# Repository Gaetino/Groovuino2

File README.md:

# Groovuino2

New version of groovuino

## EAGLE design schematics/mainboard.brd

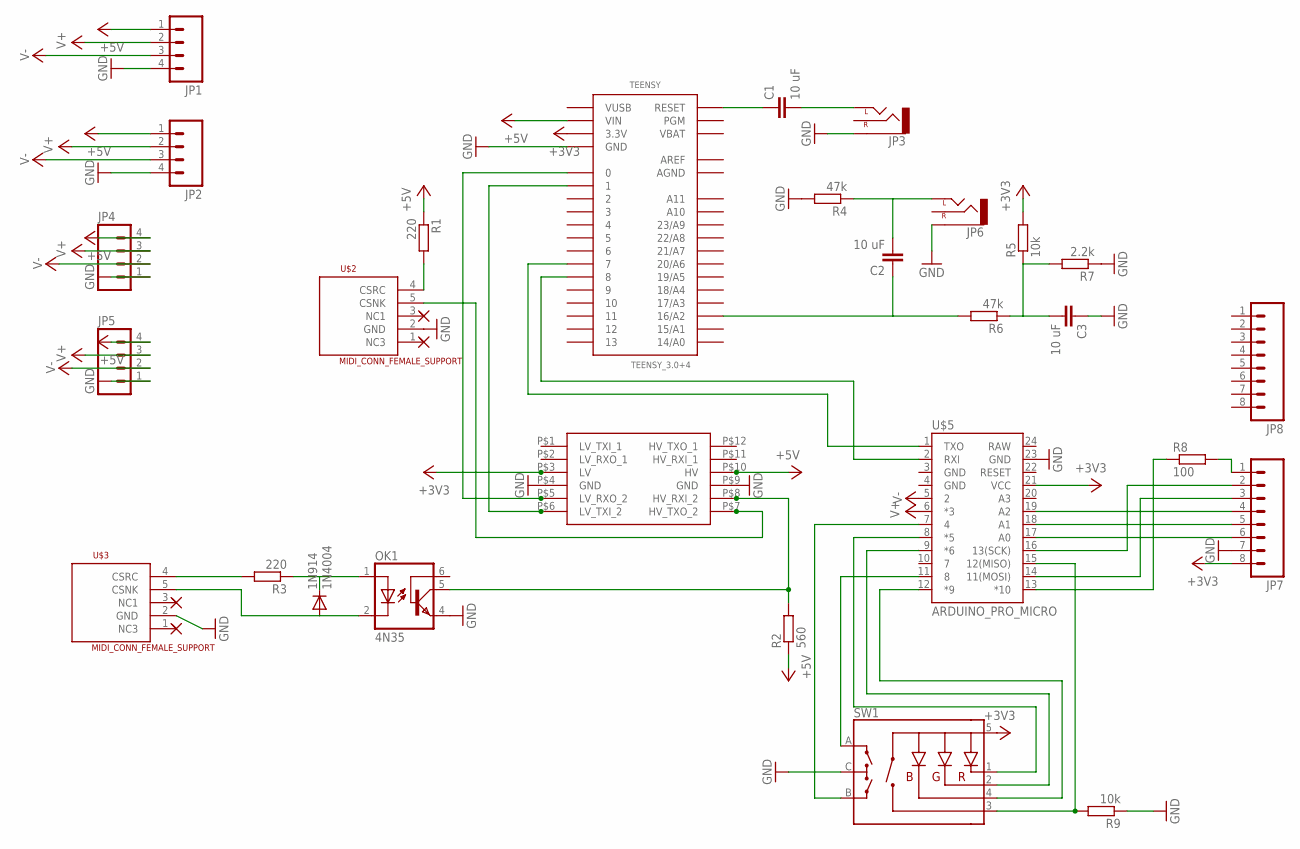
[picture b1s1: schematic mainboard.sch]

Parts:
1N914: 1N4004; DO41-10
C1, C2, C3: 10 uF; CAP-PTH-SMALL
JP1, JP2, JP4, JP5: M04PTH; 1X04
JP3, JP6: AUDIO-JACKPTH; AUDIO-JACK
JP7, JP8: M08; 1X08_ROUND
OK1: 4N35; DIL06
R1, R3: 220; 0204/5
R2: 560; 0204/5
R4, R6: 47k; 0204/5
R5, R9: 10k; 0204/5
R7: 2.2k; 0204/5
R8: 100; 0204/5
SW1: ENCODER_RGB_CA; ENCODER_LED_3
TEENSY: TEENSY_3.0+4
U$2, U$3: MIDI_CONN_FEMALE_SUPPORT; DIN_5_FEMALE_SUPPORT
U$4: LOGIC_LEVEL_CONVERTER
U$5: ARDUINO_PRO_MICRO

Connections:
+3V3: JP7.8, R5.2, SW1.5 (+), TEENSY.3.3V, TEENSY.3.3V1 (3.3V), U$4.P$3 (LV), U$5.21 (VCC)
+5V: JP1.1, JP2.1, JP4.4, JP5.4, R1.1, R2.1, TEENSY.VIN, U$4.P$10 (HV)
AGND: TEENSY.AGND
AREF: TEENSY.AREF
GND: C3.1, JP1.4, JP2.4, JP3.SLEEVE, JP4.1, JP5.1, JP6.SLEEVE, JP7.7, OK1.4 (EMI), R4.2, R7.1, R9.1, SW1.C, TEENSY.GND, TEENSY.GND1 (GND), U$2.2 (GND), U$3.2 (GND), U$4.P$4 (GND), U$4.P$9 (GND), U$5.23 (GND)
unnamed: C1.1, TEENSY.RESET
unnamed: OK1.5 (COL), R2.2, U$4.P$8 (HV_RXI_2)
unnamed: JP7.1, R8.2
unnamed: C1.2, JP3.TIP (LEFT)
unnamed: C2.2, JP6.TIP (LEFT), R4.1
unnamed: C2.1, R6.2, TEENSY.16/A2
unnamed: C3.2, R5.1, R6.1, R7.2
unnamed: R3.2, U$3.4 (CSRC)
unnamed: SW1.2 (-G), U$5.9 (*6)
unnamed: TEENSY.7, U$5.1 (TXO)
unnamed: TEENSY.8, U$5.2 (RXI)
unnamed: SW1.1 (-R), U$5.8 (*5)
unnamed: SW1.A, U$5.11 (8)
unnamed: U$2.5 (CSNK), U$4.P$7 (HV_TXO_2)
unnamed: TEENSY.1, U$4.P$6 (LV_TXI_2)
unnamed: TEENSY.0, U$4.P$5 (LV_RXO_2)
unnamed: 1N914.A, OK1.2 (C), U$3.5 (CSNK)
unnamed: 1N914.C, OK1.1 (A), R3.1
unnamed: SW1.B, U$5.7 (4)
unnamed: R9.2, SW1.3 (SW), U$5.15 (12(MISO))
unnamed: R8.1, U$5.13 (*10)
unnamed: JP7.2, U$5.16 (13(SCK))
unnamed: R1.2, U$2.4 (CSRC)
unnamed: JP7.3, U$5.14 (11(MOSI))
unnamed: SW1.4 (-B), U$5.12 (*9)
unnamed: JP7.6, U$5.17 (A0)
unnamed: JP7.5, U$5.18 (A1)
unnamed: JP7.4, U$5.19 (A2)
V+: JP1.2, JP2.2, JP4.3, JP5.3, U$5.6 (*3)
V-: JP1.3, JP2.3, JP4.2, JP5.2, U$5.5 (2)
VBAT: TEENSY.VBAT
VUSB: TEENSY.VUSB

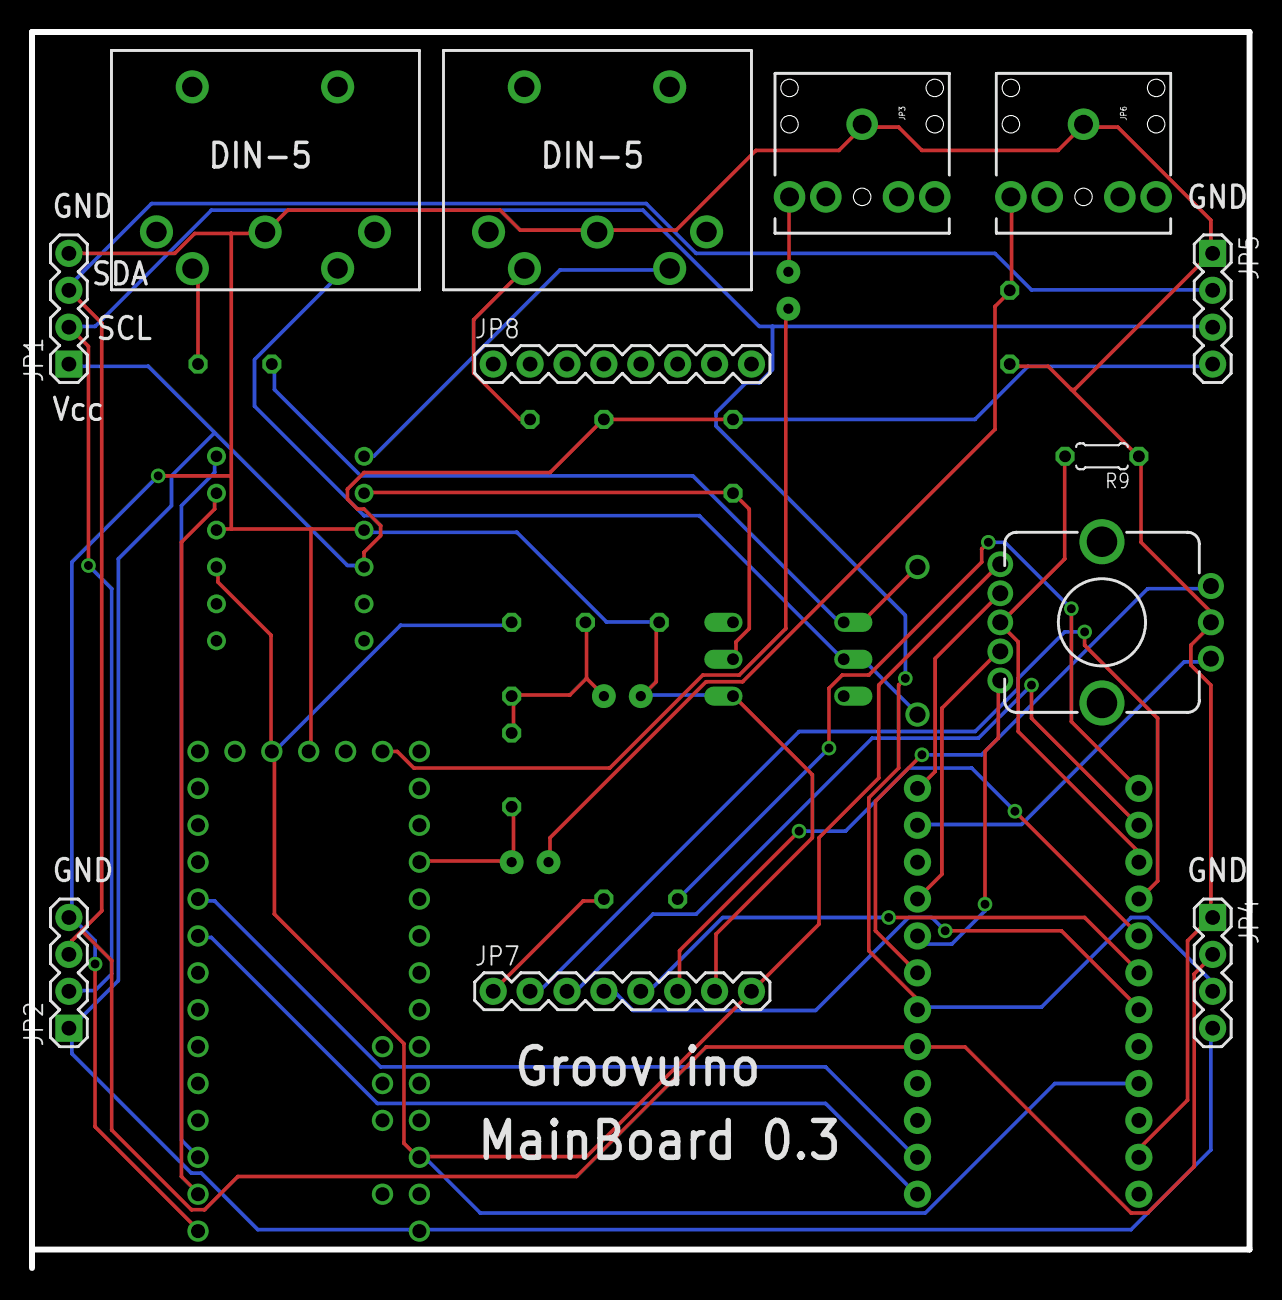
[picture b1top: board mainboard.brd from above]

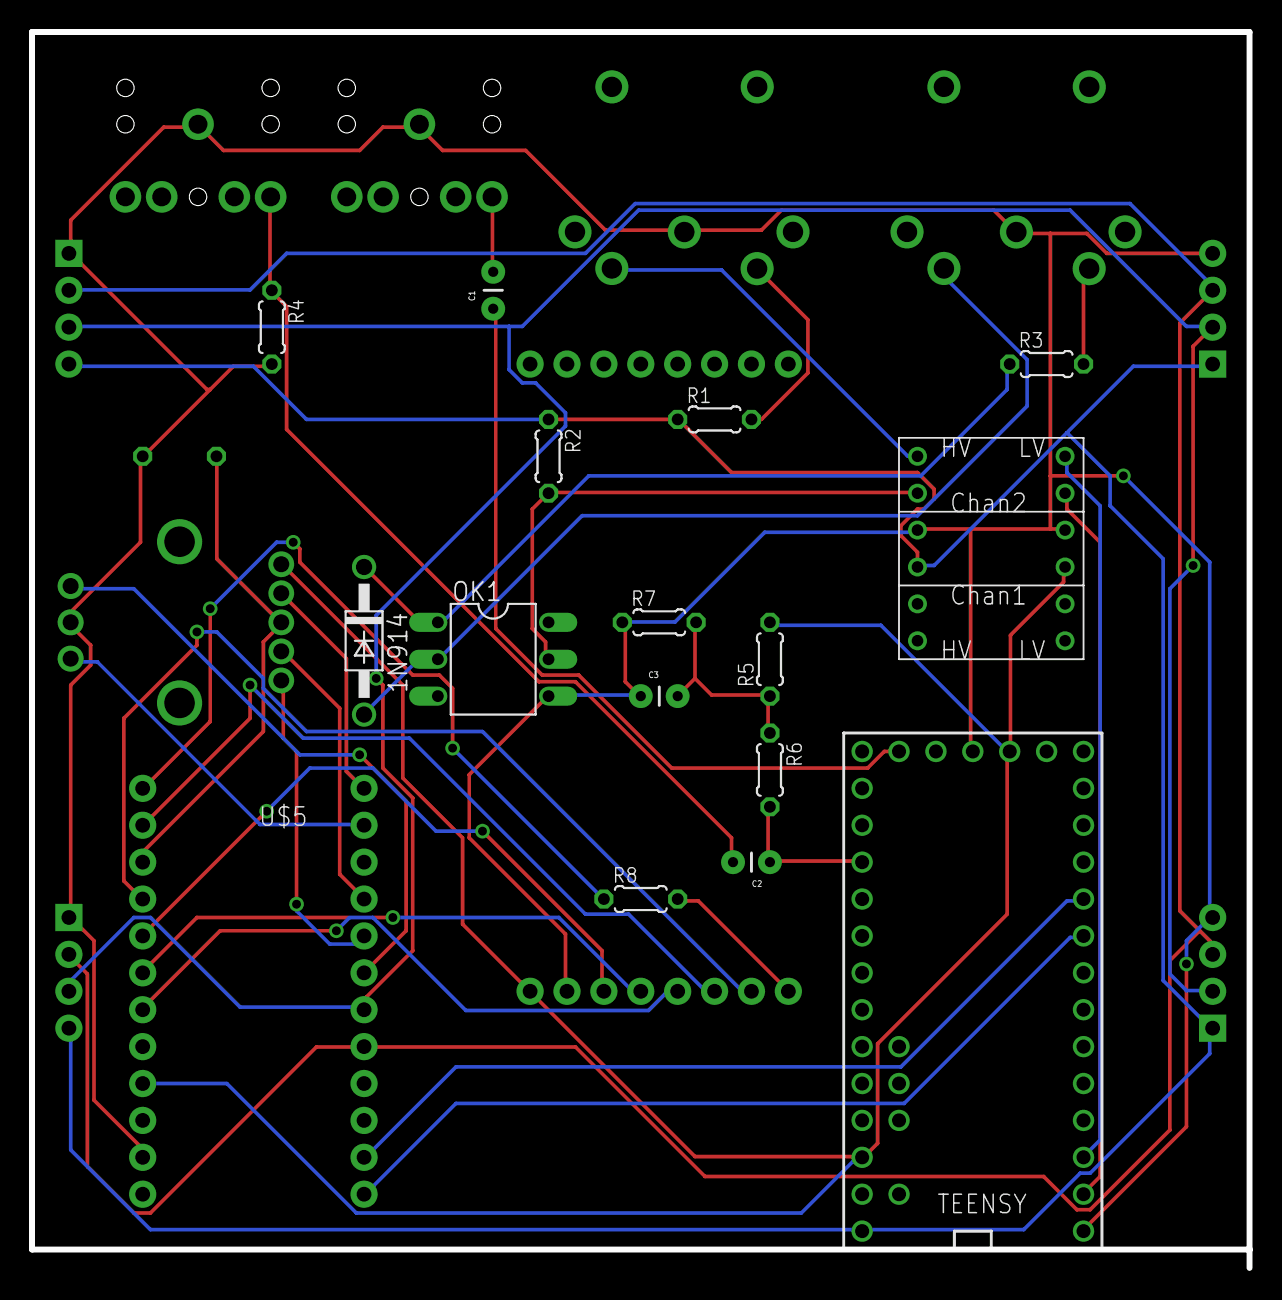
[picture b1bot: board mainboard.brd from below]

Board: 2 copper layers, 83.8 x 85.1 mm, 28 parts (16 on the bottom side), 33 nets.

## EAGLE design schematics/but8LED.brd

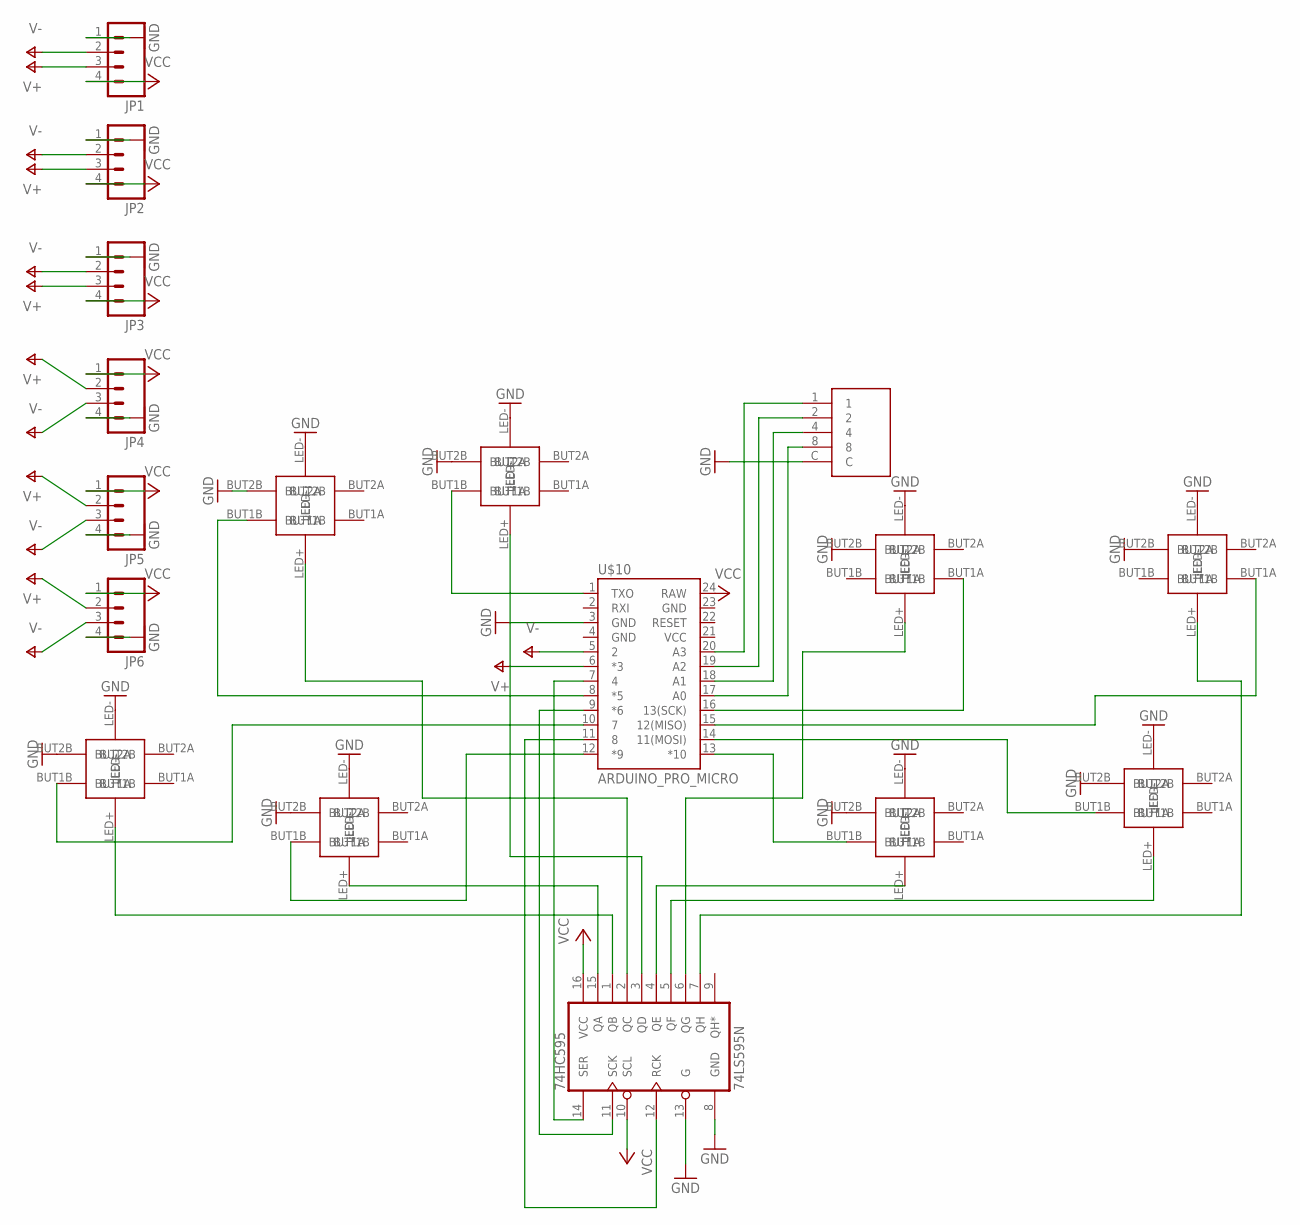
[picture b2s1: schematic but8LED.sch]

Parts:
74HC595: 74LS595N; DIL16
JP1, JP2, JP3, JP4, JP5, JP6: M04PTH; 1X04
U$1, U$2, U$3, U$4, U$5, U$6, U$7, U$8: BUTLED; LEDBUT
U$9: SWITCH16POS
U$10: ARDUINO_PRO_MICRO

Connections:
GND: 74HC595.8 (GND), 74HC595.13 (G), JP1.1, JP2.1, JP3.1, JP4.4, JP5.4, JP6.4, U$1.BUT2B, U$1.LED-, U$2.BUT2B, U$2.LED-, U$3.BUT2B, U$3.LED-, U$4.BUT2B, U$4.LED-, U$5.BUT2B, U$5.LED-, U$6.BUT2B, U$6.LED-, U$7.BUT2B, U$7.LED-, U$8.BUT2B, U$8.LED-, U$9.C, U$10.3 (GND)
unnamed: U$9.1, U$10.20 (A3)
unnamed: U$9.2, U$10.19 (A2)
unnamed: U$1.BUT1B, U$10.8 (*5)
unnamed: 74HC595.1 (QB), U$6.LED+
unnamed: U$6.BUT1B, U$10.10 (7)
unnamed: 74HC595.15 (QA), U$5.LED+
unnamed: 74HC595.2 (QC), U$1.LED+
unnamed: U$9.4, U$10.18 (A1)
unnamed: 74HC595.6 (QG), U$3.LED+
unnamed: 74HC595.7 (QH), U$4.LED+
unnamed: U$5.BUT1B, U$10.12 (*9)
unnamed: U$9.8, U$10.17 (A0)
unnamed: 74HC595.3 (QD), U$2.LED+
unnamed: U$2.BUT1B, U$10.1 (TXO)
unnamed: U$3.BUT1A, U$10.16 (13(SCK))
unnamed: U$4.BUT1A, U$10.15 (12(MISO))
unnamed: 74HC595.5 (QF), U$8.LED+
unnamed: U$8.BUT1B, U$10.14 (11(MOSI))
unnamed: 74HC595.4 (QE), U$7.LED+
unnamed: U$7.BUT1B, U$10.13 (*10)
unnamed: 74HC595.14 (SER), U$10.7 (4)
unnamed: 74HC595.11 (SCK), U$10.9 (*6)
unnamed: 74HC595.12 (RCK), U$10.11 (8)
V+: JP1.3, JP2.3, JP3.3, JP4.2, JP5.2, JP6.2, U$10.6 (*3)
V-: JP1.2, JP2.2, JP3.2, JP4.3, JP5.3, JP6.3, U$10.5 (2)
VCC: 74HC595.10 (SCL), 74HC595.16 (VCC), JP1.4, JP2.4, JP3.4, JP4.1, JP5.1, JP6.1, U$10.24 (RAW)

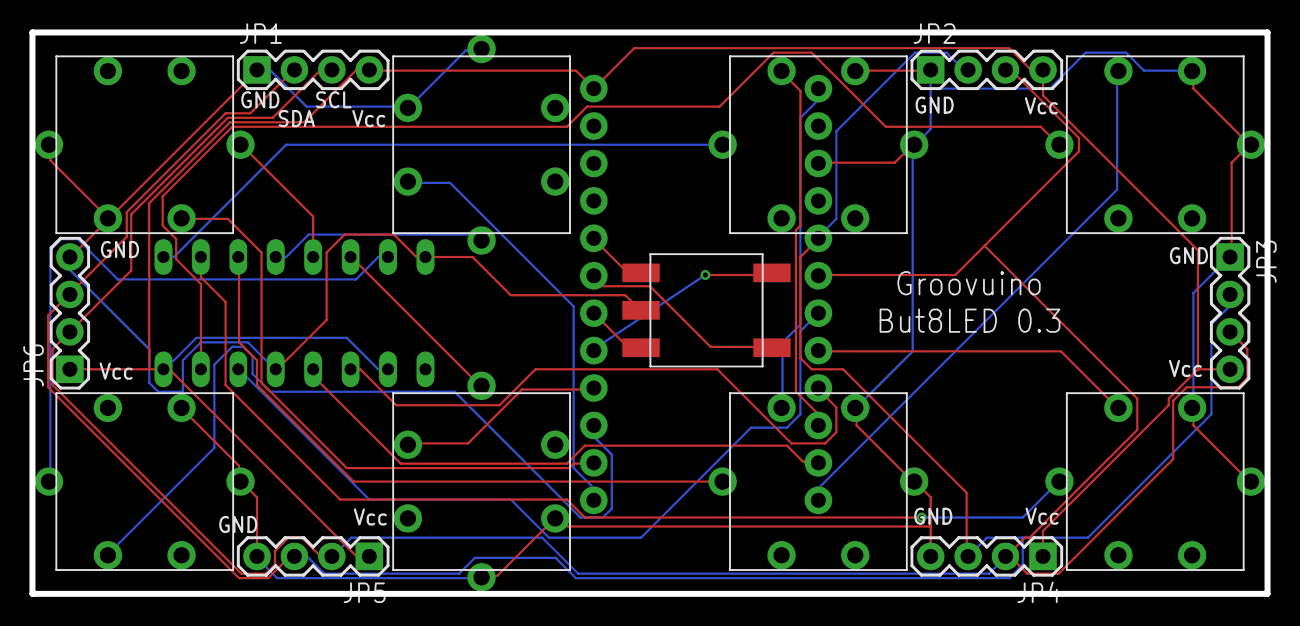
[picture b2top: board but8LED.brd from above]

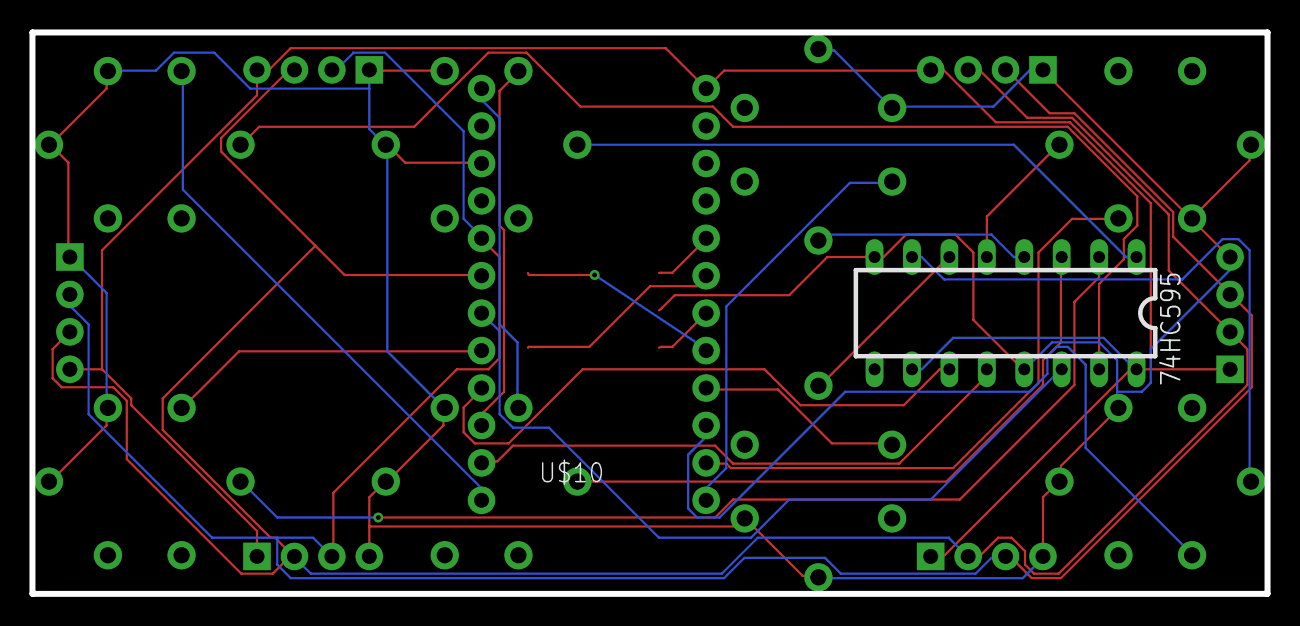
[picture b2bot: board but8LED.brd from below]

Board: 2 copper layers, 83.8 x 38.1 mm, 17 parts (2 on the bottom side), 27 nets.

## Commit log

2015-12-14 groovuino eagle library

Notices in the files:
parts and their libraries:
SparkFun-Boards: Licensing: Creative Commons ShareAlike 4.0 International - https://creativecommons.org/licenses/by-sa/4.0
